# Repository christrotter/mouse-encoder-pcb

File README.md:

# mouse-encoder-pcb
**Update, 2026/04/19:** PCB works perfectly, noise circuit excellent.

Simple standalone mouse-wheel encoder pcb, including a noise filter, but incredibly, no LED.
Designed to be VIK-friendly, and fits ALPS and TTC (and Kailh) encoders (e.g. ALPS EC10E1260502).

## Noise filter
I'd initially struggled with the noise filter on the Ultrafalcon - still getting skipped readings, doubles - but some reading indicated that I needed to change up the resistor values to meet 3.3v spec.  This is the same Bourns-recommended pattern.  

Turns out there are three camps in the noise filter arena... 
1. Only do it in software.
2. Only do it in hardware.
3. Mix of both.
... and if you are in one camp you're 'wrong' to the others.  Anyways, let's give this a shot.

## In use
Note the direction of the modeled FFC cable here...

# PCB render

# Usage example

# PCB overview

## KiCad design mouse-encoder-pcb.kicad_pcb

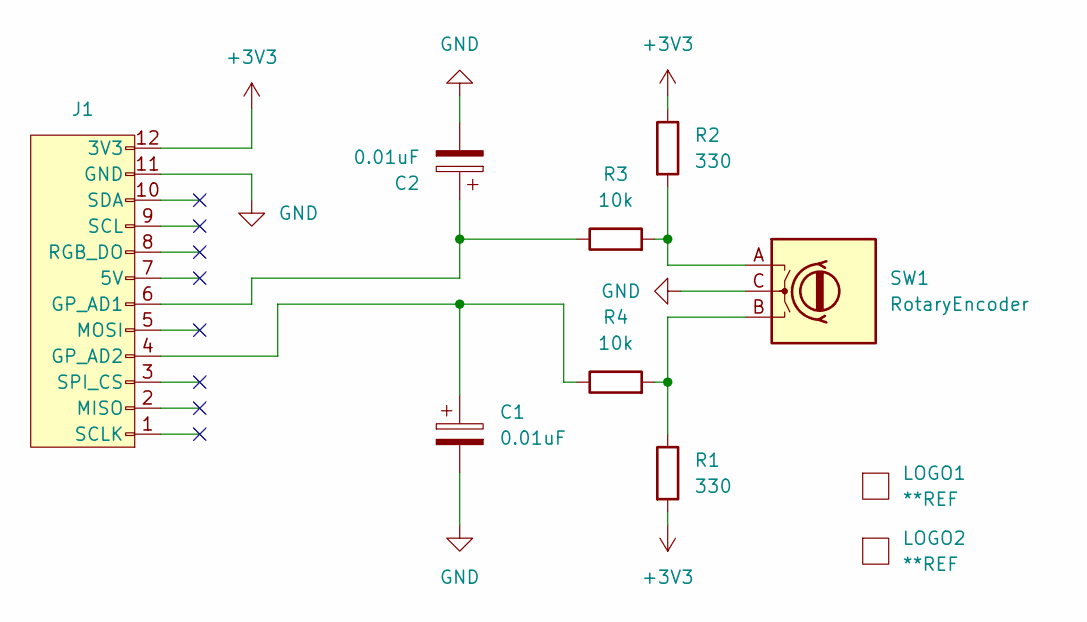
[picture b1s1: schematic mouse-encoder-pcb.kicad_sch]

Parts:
C1, C2: 0.01uF; C_0402_1005Metric
J1: vik-module-connector; FFC-SMD_FFC05001-12SBA124W5M
LOGO1: **REF; awesome-logo
LOGO2: **REF; vik-logo-small
R1, R2: 330; R_0402_1005Metric
R3, R4: 10k; R_0402_1005Metric
SW1: RotaryEncoder; SW-TH_EC10EXXXXXXX

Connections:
+3V3: J1.12 (3V3), R1.2, R2.1
GND: C1.2, C2.2, J1.11 (GND), SW1.C
unnamed: C2.1, J1.6 (GP_AD1), R3.1
unnamed: C1.1, J1.4 (GP_AD2), R4.1
unnamed: R1.1, R4.2, SW1.B
unnamed: R2.2, R3.2, SW1.A

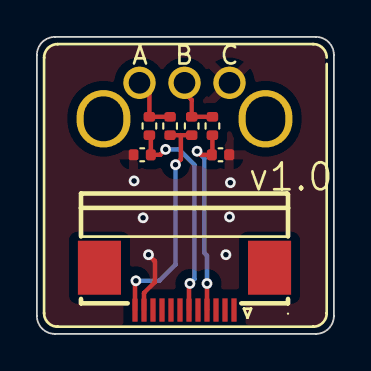
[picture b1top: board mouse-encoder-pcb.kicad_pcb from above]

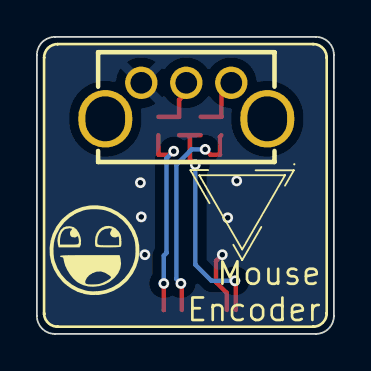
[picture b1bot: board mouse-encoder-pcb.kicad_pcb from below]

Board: 2 copper layers, 16.5 x 16.5 mm, 10 parts (3 on the bottom side), 6 nets.

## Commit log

2025-06-30 adding first rev
2025-06-30 forgot to clear a ref
2025-07-01 working square version
2025-07-12 readme bits
2025-07-12 adding step
2025-07-12 updating footprints
